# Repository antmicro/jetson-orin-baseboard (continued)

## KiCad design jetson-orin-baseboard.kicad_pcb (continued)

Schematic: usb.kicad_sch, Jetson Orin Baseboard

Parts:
C26, C27, C29, C31, C33, C36, C37, C38, C39, C45, C46, C47, C54, C55, C57, C60, C61, C62, C63: C_100n_0402; 0402-cap; MPN GRM155R61H104KE14D
C28, C30, C34, C35, C56, C59: C_10u_0402; 0402-cap; MPN CC0402MRX5R5BB106
C32: C_10u_25V_0603; 0603-cap; MPN C1608X5R1E106M080AC
C53, C58, C64, C65: C_100n_0402_50V; 0402-cap; MPN GRM155R71H104KE14D
D2, D3, D4, D5, D8, D9: LTST-C190GKT; LED_0603; MPN LTST-C190GKT
D6, D7: DF2S30FS; SOD-923; MPN DF2S30FS
D35: RB521S30T1G; SOD-523; MPN RB521S30T1G
J3: USB4105-GF-A; GCT_USB4105-GF-A; MPN USB4105-GF-A
J4: WE_632723300011_alt_symbol; WE_632723300011; MPN 632723300011
Q1, Q2, Q3: NX138BKMYL; DFN1006-3; MPN NX138BKMYL
R23, R24, R33: 4x0R_0201_array; EXB18V; MPN EXB-18VR000X
R40, R41, R56, R57, R58, R59, R60, R61, R65, R66, R67, R70, R71, R75, R76, R79, R80, R81, R82, R84: R_0R_0402; 0402-res; MPN ERJ2GE0R00X
R42, R44, R46, R47, R49, R74, R77, R83, R99: R_10k_0402; 0402-res; MPN CRCW040210K0FKEDHP
R43, R45, R105, R111: R_100k_0402; 0402-res; MPN CRCW0402100KFKEDHP
R68, R69, R72, R73, R106, R112: R_200R_0603; 0603-res; MPN ERJ-UP3F2000V
R78, R104: R_2k2_0402; 0402-res; MPN RC0402FR-072K2L
R85, R86, R87, R88, R89, R90, R91, R92, R93, R94, R95, R96, R97, R98: R_1k_0402; 0402-res; MPN CR0402-FX-1001GLF
R109, R110: R_2M0_0402; 0402-res; MPN AC0402FR-072ML
TP13, TP14, TP15, TP16, TP17, TP18, TP19, TP20, TP21, TP22, TP23, TP24, TP25, TP26, TP27, TP29: TP_SMD_0_75MM; Testpoint_smd_0_75mm
TP28: TP; TP-R-1.5
U5: FT230XQ-R; WQFN-16-1EP_4x4mm; MPN FT230XQ-R
U6: TPS65988; IC_TPS65987DDHRSHR; MPN TPS65988DHRSHR
U7: W25Q80DVUXIE_TR; USON-8_2x3mm_P0.5mm; MPN W25Q80DVUXIE TR
U8: TPS7B8133DRVR; WSON6_TI_2x2mm; MPN TPS7B8133DRVR
U9, U12: AP22615; TSOT23-6; MPN AP22615AWU-7
U10: TUSB1046-DCI; WQFN-40_1EP_6x3mm_Pitch0.4mm_EP4.7x2.7mm; MPN TUSB1046-DCIRNQT
U11, U13, U14, U15, U16: TPD4E05U06QDQARQ1; USON-10_2.5x1.0mm_P0.5mm; MPN TPD4E05U06QDQARQ1

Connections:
+1V8: Q1.1 (G), R47.2; also elsewhere on the board
+3V3: C26.1, C36.1, C37.1, C54.1, C55.1, C56.1, R49.2, R85.2, R87.2, R89.2, R91.2, R93.2, R95.2, R97.2, R106.2, R112.2, U6.5 (VIN_3V3), U10.1 (VCC), U10.6 (VCC), U10.20 (VCC), U10.28 (VCC); also elsewhere on the board
+5V: C35.1, C45.1, C57.1, C59.1, R74.2, R83.2, U6.25 (PP1_CABLE), U6.46 (PP2_CABLE), U9.6 (IN), U12.6 (IN); also elsewhere on the board
/USB Debug, DP/DRAIN1: U6.7 (DRAIN2), U6.52 (DRAIN2), U6.56 (DRAIN2), U6.57 (DRAIN2)
/USB Debug, DP/DRAIN2: U6.8 (DRAIN1), U6.15 (DRAIN1), U6.19 (DRAIN1), U6.58 (DRAIN1)
/USB Debug, DP/FLASH_CLK: R23.7, U7.6 (SCLK)
/USB Debug, DP/FLASH_MISO: R24.7, R24.8, U7.2 (SO/IO1)
/USB Debug, DP/FLASH_MOSI: R23.8, U7.5 (SI/IO0)
/USB Debug, DP/FTDI_3V3: C27.1, C29.1, C34.1, R46.2, R72.2, R73.2, U5.1 (VCCIO), U5.8 (3V3OUT), U5.10 (VCC), U8.6 (OUT)
/USB Debug, DP/FTDI_CBUS0: TP15.1, U5.12 (CBUS0)
/USB Debug, DP/FTDI_CBUS3: TP16.1, U5.14 (CBUS3)
/USB Debug, DP/FTDI_LED_RX: D3.2, U5.11 (CBUS1)
/USB Debug, DP/FTDI_LED_TX: D2.2, U5.5 (CBUS2)
/USB Debug, DP/HPDIN: R75.2, U10.32 (HPDIN/RSVD2)
/USB Debug, DP/LDO_3V3: D35.2
/USB Debug, DP/PDC_ADCIN1: R42.1, R43.2, U6.6 (ADCIN1)
/USB Debug, DP/PDC_ADCIN2: R44.1, R45.2, U6.10 (ADCIN2)
/USB Debug, DP/PDC_CTL0: R33.4, U6.18 (GPIO2)
/USB Debug, DP/PDC_CTL1: R33.2, U6.16 (GPIO0)
/USB Debug, DP/PDC_FLIP: R33.3, U6.17 (GPIO1)
/USB Debug, DP/PDC_GPIO14: R68.2, U6.42 (GPIO14/PWM1)
/USB Debug, DP/PDC_GPIO15: R69.2, U6.43 (GPIO15/PWM2)
/USB Debug, DP/PDC_HPD1: R65.2, U6.30 (GPIO3/HPD1)
/USB Debug, DP/PDC_I2C1_IRQn: TP17.1, U6.29 (~I2C1_IRQ)
/USB Debug, DP/PDC_I2C1_SCL: R70.2, U6.27 (I2C1_SCL)
/USB Debug, DP/PDC_I2C1_SDA: R71.2, U6.28 (I2C1_SDA)
/USB Debug, DP/PDC_I2C2_IRQn: TP18.1, U6.34 (~I2C2_IRQ)
/USB Debug, DP/PDC_I2C2_SCL: TP19.1, U6.32 (I2C2_SCL)
/USB Debug, DP/PDC_I2C2_SDA: TP20.1, U6.33 (I2C2_SDA)
/USB Debug, DP/PDC_I2C3_SCL: R66.2, U6.21 (I2C3_SCL/GPIO5)
/USB Debug, DP/PDC_I2C3_SDA: R67.2, U6.22 (I2C3_SDA/GPIO6)
/USB Debug, DP/PDC_LDO_1V8: C28.1, U6.35 (LDO_1V8)
/USB Debug, DP/PDC_LDO_3V3: C30.1, R42.2, R44.2, U6.9 (LDO_3V3)
/USB Debug, DP/PDC_RESET: R41.2, U6.44 (HRESET)
/USB Debug, DP/USBC0_5V_PEN: R84.1, U6.49 (GPIO17/PP_EXT2)
/USB Debug, DP/USBC0_CC1: J4.A5 (CC1), U6.45 (C2_CC1), U16.5 (IO4), U16.6 (IO4)
/USB Debug, DP/USBC0_CC2: J4.B5 (CC2), U6.47 (C2_CC2), U16.4 (IO3), U16.7 (IO3)
/USB Debug, DP/USBC0_CONN_TX1_N: C60.2, J4.A3 (TX1-), U15.5 (IO4), U15.6 (IO4)
/USB Debug, DP/USBC0_CONN_TX1_P: C62.2, J4.A2 (TX1+), U15.4 (IO3), U15.7 (IO3)
/USB Debug, DP/USBC0_CONN_TX2_N: C61.2, J4.B2 (TX2+), U14.4 (IO3), U14.7 (IO3)
/USB Debug, DP/USBC0_CONN_TX2_P: C63.2, J4.B3 (TX2-), U14.5 (IO4), U14.6 (IO4)
/USB Debug, DP/USBC0_CTL0: R33.6, R82.1, U10.22 (CTL0/SDA)
/USB Debug, DP/USBC0_CTL1: R33.5, U10.23 (CTL1/HPDIN)
/USB Debug, DP/USBC0_DPEQ0: R91.1, R92.1, U10.14 (DPEQ0/A1)
/USB Debug, DP/USBC0_DPEQ1: R93.1, R94.1, U10.2 (DPEQ1)
/USB Debug, DP/USBC0_EQ0: R95.1, R96.1, U10.38 (EQ0)
/USB Debug, DP/USBC0_EQ1: R97.1, R98.1, U10.35 (EQ1)
/USB Debug, DP/USBC0_FLG: R83.1, TP29.1, U12.3 (FLG)
/USB Debug, DP/USBC0_FLIP: R33.7, R79.1, U10.21 (FLIP/SCL)
/USB Debug, DP/USBC0_I2C_EN: R85.1, R86.1, U10.17 (I2C_EN)
/USB Debug, DP/USBC0_RX1_N: J4.B11 (RX1+), U10.31 (RX1_N), U15.2 (IO2), U15.9 (IO2)
/USB Debug, DP/USBC0_RX1_P: J4.B10 (RX1-), U10.30 (RX1_P), U15.1 (IO1), U15.10 (IO1)
/USB Debug, DP/USBC0_RX2_N: J4.A10 (RX2-), U10.39 (RX2_N), U14.1 (IO1), U14.10 (IO1)
/USB Debug, DP/USBC0_RX2_P: J4.A11 (RX2+), U10.40 (RX2_P), U14.2 (IO2), U14.9 (IO2)
/USB Debug, DP/USBC0_SBU1: J4.A8 (SBU1), R109.2, U10.27 (SBU1), U13.2 (IO2), U13.9 (IO2)
/USB Debug, DP/USBC0_SBU2: J4.B8 (SBU2), R110.2, U10.26 (SBU2), U13.1 (IO1), U13.10 (IO1)
/USB Debug, DP/USBC0_SSEQ0: R87.1, R88.1, U10.11 (SSEQ0/A0)
/USB Debug, DP/USBC0_SSEQ1: R89.1, R90.1, U10.3 (SSEQ1)
/USB Debug, DP/USBC0_TX1_N: C60.1, U10.34 (TX1_N)
/USB Debug, DP/USBC0_TX1_P: C62.1, U10.33 (TX1_P)
/USB Debug, DP/USBC0_TX2_N: C61.1, U10.36 (TX2_N)
/USB Debug, DP/USBC0_TX2_P: C63.1, U10.37 (TX2_P)
/USB Debug, DP/USBC0_VBUS: C65.1, D7.1, J4.A4 (VBUS), J4.A9 (VBUS), J4.B4 (VBUS), J4.B9 (VBUS), Q3.1 (G), R111.2, U6.3 (VBUS2), U12.1 (OUT)
/USB Debug, DP/USBC3_5V_PEN: R76.1, U6.48 (GPIO16/PP_EXT1)
/USB Debug, DP/USBC3_CC1: J3.A5 (CC1), U6.24 (C1_CC1), U11.5 (IO4), U11.6 (IO4)
/USB Debug, DP/USBC3_CC2: J3.B5 (CC2), U6.26 (C1_CC2), U11.4 (IO3), U11.7 (IO3)
/USB Debug, DP/USBC3_FLG: R74.1, TP27.1, U9.3 (FLG)
/USB Debug, DP/USBC3_VBUS: C32.1, C64.1, D6.1, J3.A4 (VBUS), J3.A9 (VBUS), J3.B4 (VBUS), J3.B9 (VBUS), Q2.1 (G), R105.2, U6.13 (VBUS1), U8.1 (IN), U8.2 (EN), U9.1 (OUT)
/USB Debug, DP/USBC_HPD1: Q1.3 (D), R49.1, R65.1, R75.1
/USB Debug, DP/USBPD_SCL: R61.1, R66.1, R70.1, R79.2
/USB Debug, DP/USBPD_SDA: R60.1, R67.1, R71.1, R82.2
/USB Debug, DP/USBSS0_RX_C_N: C38.2, U10.4 (SSRX_N)
/USB Debug, DP/USBSS0_RX_C_P: C46.2, U10.5 (SSRX_P)
/USB Debug, DP/USBSS0_TX_C_N: C39.2, U10.7 (SSTX_N)
/USB Debug, DP/USBSS0_TX_C_P: C47.2, U10.8 (SSTX_P)
/USB Debug, DP/USB_FTDI_N: R80.2, U5.7 (USBDM)
/USB Debug, DP/USB_FTDI_P: R81.2, U5.6 (USBDP)
/USB Debug, DP/~PFLASH_CS: R24.5, U7.1 (~CS)
/USB Debug, DP/~PFLASH_HOLD: R23.6, U7.7 (~HOLD/IO3)
/USB Debug, DP/~PFLASH_WP: R24.6, U7.3 (~WP/IO2)
DEBUG_RXD: R56.1; also elsewhere on the board
DEBUG_TXD: R57.1; also elsewhere on the board
DP1_AUX_N: U10.25 (AUX_N); also elsewhere on the board
DP1_AUX_P: U10.24 (AUX_P); also elsewhere on the board
DP1_HPD: R40.1; also elsewhere on the board
DP1_TXD0_N: U10.10 (DP0_N); also elsewhere on the board
DP1_TXD0_P: U10.9 (DP0_P); also elsewhere on the board
DP1_TXD1_N: U10.13 (DP1_N); also elsewhere on the board
DP1_TXD1_P: U10.12 (DP1_P); also elsewhere on the board
DP1_TXD2_N: U10.16 (DP2_N); also elsewhere on the board
DP1_TXD2_P: U10.15 (DP2_P); also elsewhere on the board
DP1_TXD3_N: U10.19 (DP3_N); also elsewhere on the board
DP1_TXD3_P: U10.18 (DP3_P); also elsewhere on the board
EEPROM_PWR: C33.1, D35.1, R23.3, R24.1, R24.3, TP21.1, U7.8 (VCC); also elsewhere on the board
GND: C26.2, C27.2, C28.2, C29.2, C30.2, C31.2, C32.2, C33.2, C34.2, C35.2, C36.2, C37.2, C45.2, C53.2, C54.2, C55.2, C56.2, C57.2, C58.2, C59.2, C64.2, C65.2, D4.2, D5.2, D6.2, D7.2, J3.A1 (GND), J3.A12 (GND), J3.B1 (GND), J3.B12 (GND), J3.S1 (SHIELD), J4.A1 (GND), J4.A12 (GND), J4.B1 (GND), J4.B12 (GND), J4.Shell (SHIELD), Q2.2 (S), Q3.2 (S), R41.1, R43.1, R45.1, R77.1, R78.1, R86.2, R88.2, R90.2, R92.2, R94.2, R96.2, R98.2, R99.1, R104.1, R105.1, R109.1, R110.1, R111.1, TP26.1, U5.3 (GND), U5.13 (GND), U5.17 (GND), U6.20 (GND), U6.51 (GND), U6.59 (GND_EP), U7.4 (VSS), U8.3 (GND), U8.4 (GND), U8.7 (GND), U9.2 (GND), U10.41 (EP_GND), U11.3 (GND), U11.8 (GND), U12.2 (GND), U13.3 (GND), U13.8 (GND), U14.3 (GND), U14.8 (GND), U15.3 (GND), U15.8 (GND), U16.3 (GND), U16.8 (GND); also elsewhere on the board
unnamed: C31.1, R46.1, U5.9 (~RESET)
unnamed: D2.1, R72.1
unnamed: D3.1, R73.1
unnamed: D4.1, R68.1
unnamed: D5.1, R69.1
unnamed: D8.1, R106.1
unnamed: D8.2, Q2.3 (D)
unnamed: D9.1, R112.1
unnamed: D9.2, Q3.3 (D)
unnamed: Q1.2 (S), R40.2, R47.1
unnamed: R56.2, U5.15 (TXD)
unnamed: R57.2, U5.2 (RXD)
unnamed: R58.2, U5.16 (~RTS)
unnamed: R59.2, U5.4 (~CTS)
unnamed: R76.2, R77.2, U9.4 (EN)
unnamed: R78.2, U9.5 (ISET)
unnamed: R84.2, R99.2, U12.4 (EN)
unnamed: R104.2, U12.5 (ISET)
unnamed: TP13.1, U6.31 (GPIO4/HPD2)
unnamed: TP14.1, U6.23 (~I2C3_IRQ/GPIO7)
unnamed: TP28.1, U10.29 (CAD_SNK/RSVD1)
PDC_MISO: R24.2, TP23.1, U6.36 (SPI_POCI/GPIO8); also elsewhere on the board
PDC_MOSI: R23.1, TP22.1, U6.37 (SPI_PICO/GPIO9); also elsewhere on the board
PDC_SCLK: R23.2, TP24.1, U6.38 (SPI_CLK/GPIO10); also elsewhere on the board
PWR_SOFT: R58.1; also elsewhere on the board
SYS_SCL: R61.2; also elsewhere on the board
SYS_SDA: R60.2; also elsewhere on the board
USB0_D_N: J4.A7 (D-), J4.B7 (D-), U16.2 (IO2), U16.9 (IO2); also elsewhere on the board
USB0_D_P: J4.A6 (D+), J4.B6 (D+), U16.1 (IO1), U16.10 (IO1); also elsewhere on the board
USBPD1_HV: C53.1, U6.11 (PP_HV1); also elsewhere on the board
USBPD2_HV: C58.1, U6.1 (PP_HV2); also elsewhere on the board
USBSS0_RX_N: C46.1; also elsewhere on the board
USBSS0_RX_P: C38.1; also elsewhere on the board
USBSS0_TX_N: C47.1; also elsewhere on the board
USBSS0_TX_P: C39.1; also elsewhere on the board
~PDC_CS: R24.4, TP25.1, U6.39 (~SPI_CS/GPIO11); also elsewhere on the board

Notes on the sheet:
USB-UART Bridge
POWER DOWN
USB PD Controller
USB-PD Source/Sink
USB-C 0 Display Port alt mode
4 LANE DP
CONFIGURATION
USBC0
Debug USB-C 3
USB + 2 LANE DP
USBC3
CTL0
CTL1
USB ONLY

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
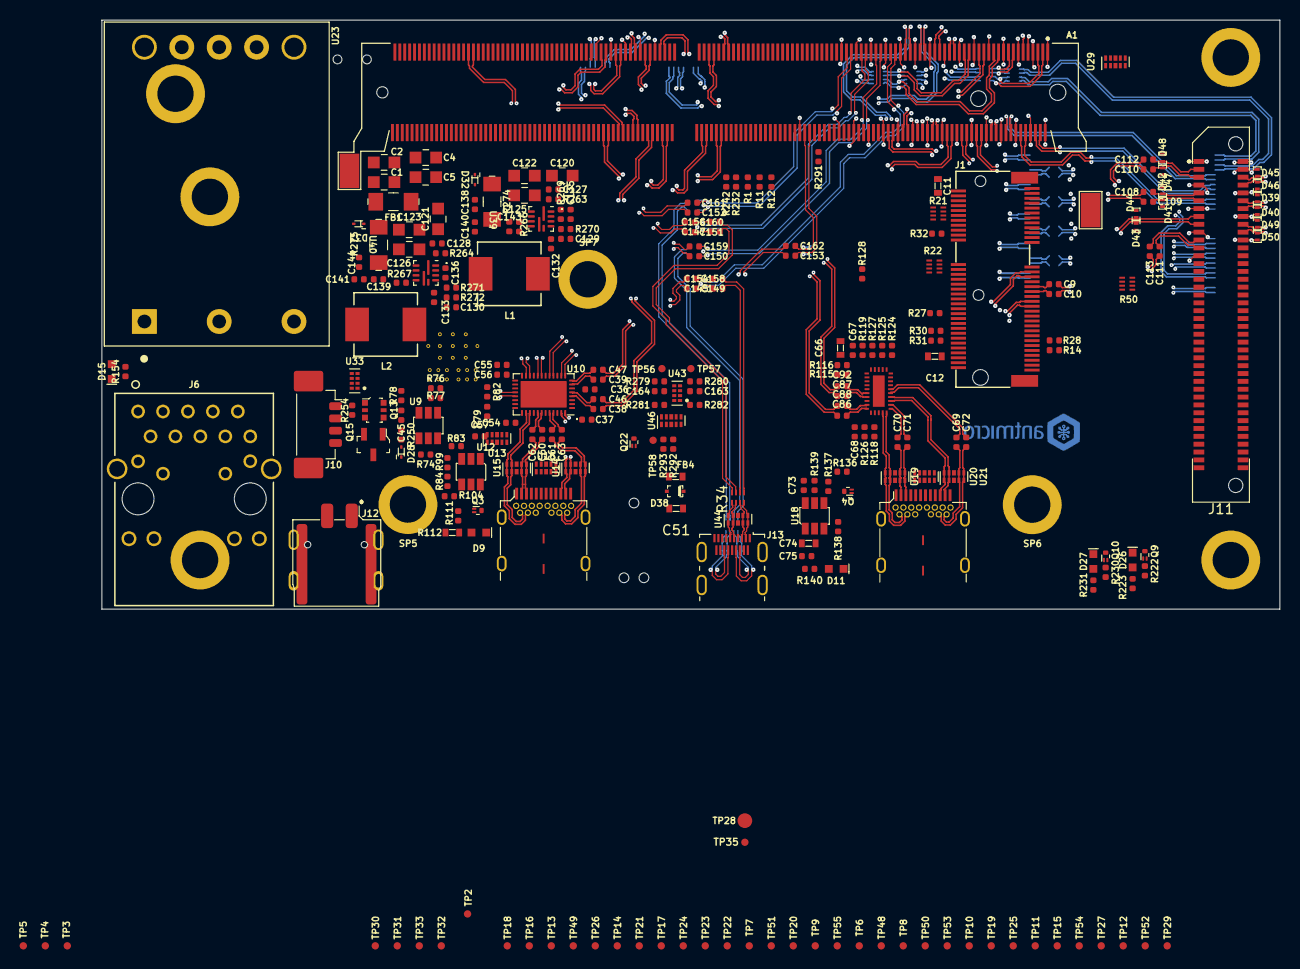
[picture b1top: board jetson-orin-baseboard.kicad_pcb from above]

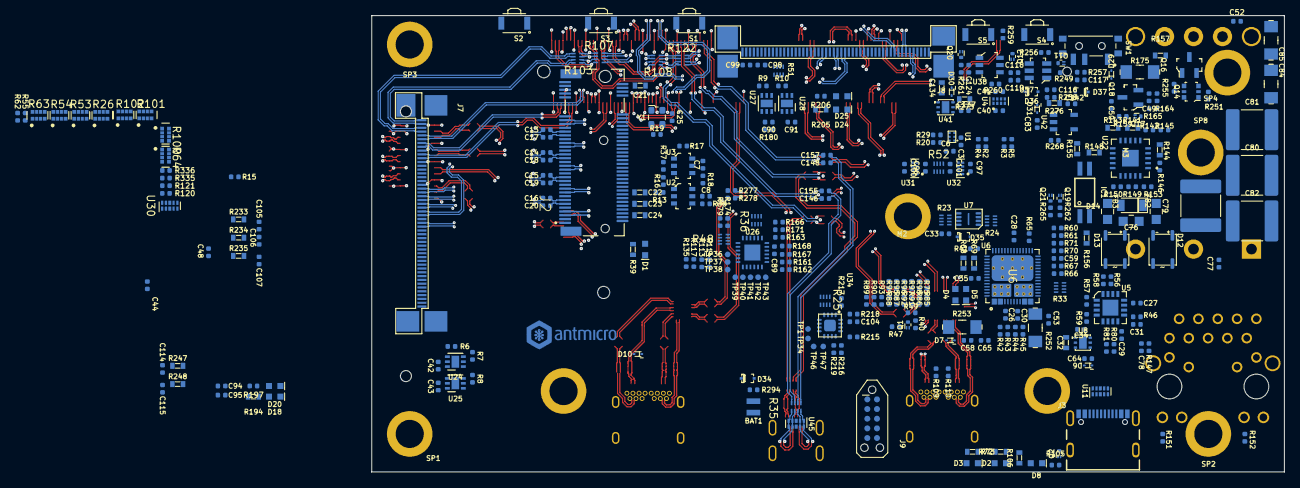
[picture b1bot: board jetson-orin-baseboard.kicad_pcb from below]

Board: 8 copper layers, 120.0 x 60.0 mm, 587 parts (331 on the bottom side), 599 nets.

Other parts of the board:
kibuzzard-633EE390: G***; kibuzzard-633EE390

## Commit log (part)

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2023-02-09 Enumerate resistors
2023-02-09 Replace buttons on PCB. Update VBUS led circuitry. Improve power planes
2023-02-09 Continue moving signals to accomodate new switch position
2023-02-10 Continue routing after changes
2023-02-13 Update PCB from schematics. Recover deleted footprints
2023-02-14 Clear space under new HDMI connector
2023-02-14 Change tag-connect to 2x5 pin 1.27 header
2023-02-14 Import changes from schematics. Finish signal routing
2023-02-14 Cleanup PCB with cleanup tool
2023-02-14 Minor layout improvements
2023-02-15 Start tunning high speed traces
2023-02-16 Add more capacitors to the SoM VDD_IN
2023-02-16 Place caps and resistors on PCB
2023-02-16 Fix custom design rules for differential pair
2023-02-16 Fix intra-pair sqew errors
2023-02-16 Route CSI_B_EN signal on bottom layer only
2023-02-17 Connect USB-C HPD to correct pin
2023-02-17 Place tag connect on the PCB. Update layout after recent schematic changes
2023-02-21 Import changes to PCB. Cleanup space for DP mux
2023-02-23 Routed DP++ signals to the display mux
2023-02-24 Added 499 Ohm resistors required for HDMI
2023-02-24 Added alternative DNP circuitry to make DP priority
2023-02-28 Fix SDA/SCL cross
2023-02-28 Replace 1u/10V cap with 1u/25V one
2023-02-28 Add capacitors to USB SS. Add VBUS, _HV 1u/4u7 caps. Improve readability
2023-02-28 Update J8 VSYNC singal assigment
2023-03-01 Add ESD protection to force recovery button
2023-03-01 Add 10k pullups to I2C1/I2C2 signals
2023-03-01 Add 220k pullups to HD3SS3220 OUTx pins
2023-03-01 Add TVS to the J14
2023-03-01 Minor readability improvements
2023-03-01 Update PCM12SMTR symbol
2023-03-01 Add resistor to slow down discharge of U37 2A input. Add TVS to S4 and S5
2023-03-01 Clarify auto startup comments
2023-03-01 Annotate parts, import them on PCB
2023-03-01 Start placement of the new components
2023-03-02 Simplify U6 I2C connection. Adjust pinout on R80/R81 remove flash R0 arrays
2023-03-02 Flip connections on R26 and R63 for easier routing
2023-03-02 Adjust connections on R130 for easier routing
2023-03-02 Improve clearance around PoE signals
2023-03-02 Minor improvements around U10
2023-03-02 Simplify routing around J11
2023-03-02 Improve U34 fanout
2023-03-02 Add thermal relief for M.2 key E and CSI A
2023-03-03 Fix silks warnings
2023-03-03 Add labels to M.2 connectors and ETH
2023-03-03 Bump revision to 1.1.0
2023-03-03 Add USB_ID controll from USB-C1 VBUS. Clarify notes
2023-03-03 Implement changes on PCB
2023-03-03 Fix M.2 Key M label
2023-03-06 Set R199 and R229 as DNP. U23 has builtin pullup on CTRL pin
2023-03-06 Connect power switches FLG pins to the GPIO expander
2023-03-06 Use AP22615 as CSI e-fuse
2023-03-06 Enumerate components. Import to PCB. Update layout with new components
2023-03-06 Minor via improvements around 5V and 3.3V DCDC
2023-03-08 Add diagram to readme
2023-03-08 Use PNG diagram in readme
2023-03-08 Set USB_PD_IRQ label as output on usb subsheet
2023-03-08 Update CSIA/B_FLG label naming
2023-03-08 Update HD3SS3220 and TPS65988 IRQ pins circuitry to use 1.8V singaling
2023-03-08 Update layout after schematic changes. Place components, clear DRC and silks
2023-04-11 README: rephrase, mention Jetson Orin Nano
2023-07-05 Ethernet Simplification
2023-10-16 Introduce component standardization
2023-10-20 Fixed HDMI 3d model offset
2023-11-06 Updated few symbols/footprints with newest version from the library
2023-11-06 Add OHP assets
2023-11-06 Add stackup.csv
2024-01-05 [#53466] pcb: swap CSIA_5V and CSIA_3V3 LEDs labels
2024-01-05 [#53466] pcb: use ${REVISION} in the revision string on PCB
2024-03-22 [#56923] Update symbol/footprint links; Migrate to KiCad 7
2024-03-26 [#56923] Fix OHP issue
2024-03-26 [#56923] Loclib
2024-03-27 Update assets
2024-03-29 [#56923] Cleaned up DRC, restored old H2.5mm footprint
2024-03-29 [#56923] Restored DRC and minor designator cleanup
2024-05-27 [#59786] Update SoM standoffs
2024-05-27 [#59786] Exclude J9 from BoM
2024-05-28 [#60110] Add BAT1 polarity marking
2024-05-29 [#60168] Update TagConnect symbol and footprint
2024-05-29 [#60168] Update R_499R_0402 and R_887k_0402 from library
2024-05-29 [#60168] Update Y1, BA1, C_47p_0402 symbols and footprints
2024-05-29 [#60168] Update SoM connector symbol and footprint
2024-05-29 [#60168] Update C_47p_0402 symbols and footprints
2024-06-03 [#60168] Update C_220n_0402 symbols and footprints
2024-06-03 [#60168] Update LED_G_0603_LTST-C190GKT symbols
2024-06-04 [#60168] Update Tag-Connect_TC2050 symbols and footprints
2024-06-04 [#60168] Change the DDR4 socket footprint from Bus_DDR4_SODIMM_TE_2309413 to TE_2309413
2024-06-04 [#60168] Update coper logos to global lib
2024-06-05 [#60168] Revert D54 position
2024-06-05 [#60168] Fix silkscreen warnings
2024-06-05 [#60168] Relink 3D modles to global lib, assign missing 3D models
2024-06-05 [#60168] Improve passive components silkscreen
2024-06-05 [#60168] Add comment about DC in connector
2024-06-13 [#60110] Add PoE netclass. Increase PoE clereance
2024-06-14 [#60110] Fixed HS routing. Fixed silkscreen
2024-06-14 [#60110] Updated pdf schematics
2024-06-14 [#60110] Updated VCC_CONN voltage description
2024-07-01 README: Update OHP links, bump copyright date
2024-07-01 [#61641] Update TPS65988DHRSHR footprint
2024-07-01 [#61641] Updated pcb fill
2024-07-26 Add documentation for GitHub Pages
2024-07-26 Fix J3 on IO map
2024-07-29 Add 3D renders presenting board connections
2024-07-30 Rename docs folder
2024-07-30 README: Update doc folder name
2024-07-30 Updated renders and altered description of power supply connection
2024-07-30 update 8e9fef7b4b0b629bf49db563b7ea2beb83c7b6ea
2024-08-16 [#61587] Layout update after DRC adjustment
2024-08-16 [#61587] Fix length matching. Bump revision to 1.1.7
2024-08-16 [#61587] Synchronize component instances
2024-08-16 [#61587] Cleanup design after component synchronization
2024-08-16 [#61587] Correct R42 value back to 10k
2024-08-16 [#61587] Add power flags on schematic
2024-08-16 [#61587] Add polarity marking on Molex Nano-Fit connector
2024-08-19 [#63764] Minor language fixes
2024-08-23 64668 Describe USB-C as a recommended power supply option
2024-08-29 [#64774] upload assets
2024-08-29 Include recent updates to docs
2024-08-29 Add referenced images and links to docs
2024-09-02 [#64687] Fix references
2024-09-03 [#64267] Remove local symbol and footprint paths
2024-09-03 [#64267] Remove old DC-DC converters from PCB, start layout of new ones
2024-09-03 [#64267] Change resistors to set the PD controller to configuration 3
2024-09-03 [#64267] Swap 5V and 3V3 converter placement
2024-09-03 [#64267] Layout components for +5V power path
2024-09-03 [#64267] Try new component placement of 3V3 converter, new coil
2024-09-03 [#64267] Replace the coil for the 5V converter
2024-09-03 [#64267] Finish layout of 3V3 converter
2024-09-03 [#64602] Fix some tracks and silkscreen
2024-09-03 [#64602] Add resistor divider for UVLO for 5V converter, repair last broken tracks, adjust silkscreen
2024-10-07 [#64602] Update component footprints from library, increase clearance between GND and 3V3 switching node, clear DRC
2024-10-07 [#64336] Update SPI net names
2024-10-07 [#64336] Add tag connect pinout on silkscreen
2024-10-07 [#64336] Update SPI connector pinout, finish layout
2024-10-07 [#64336] Align component designators and restore missing logos
2024-10-07 [#64336] Swap SPI and I2C information on silkscreen
2024-10-07 [#64336] Move R112 to the bottom
2024-10-07 [#64336] Clear DRC
2024-10-07 [#64336] Improve R131 connection
2024-10-07 [#64790] Move C130, adjust designators, upgrade tespoints markings
2024-10-07 [#64790] Adjust designators and polygons, improve tespoints
2024-10-07 [#64790] Clean DRC
2024-10-07 [#64336] Align text fields inside the SPI pinout
2024-10-07 [#64928] Implemented fixes after layout review
2024-10-07 [#64928] Implement fixes after schematic review
2024-10-07 [#64928] Correct names of fiducials on PCB, add not in schematic property to all of them
2024-10-07 Updated assets for rev. 1.1.8
2024-10-07 [#64928] Relocate test points to accessible areas
2024-10-07 [#64928] Add more test points, small tweaks on silkscreen layers
2024-10-07 Updated docs to reflect changes in rev. 1.1.8
2024-10-07 [#64928] Update footprints from library, clean DRC and ERC
2024-10-07 [#64928] Place components, start routing signals
2024-10-07 [#64928] Add DNP 10M pulldown to Q20, fix note, Replace U29 with NTS0102GT
2024-10-07 [#66619] Update layout
2024-10-07 [#64928] Align designators
2024-10-07 [#66619] Refresh assets
2024-10-14 [#67155] Fix annular ring on Inner copper 1 layer
2024-10-14 [#67155] Bump project date
2024-10-14 [#67155] Bump rev to 1.2.0
2024-10-14 [#67155] Exclude 5V DCDC coil overlap DRC
2024-10-14 [#67155] Add pin driven errors to exclusions
2024-10-14 [#67155] Update unactual component symbols
2024-10-14 [#67155] Update ERC
2024-10-14 [#67155] Update PCB from schematic
2024-10-15 [#67155] Update expansion connector VCC comment
2024-10-15 [#67339] Add custom rule for hole to track clearance
2024-10-15 [#67339] Resize vias to 0.2hole, update filled zones
2024-10-16 [#67339] Remove custom rule
2024-10-16 [#67339] Resize vias to 0.1mm hole, bump revision
2024-10-17 [#67339] Update USB3 mode selector frame
2024-10-17 [#67339] Update connections on In1.Cu
2024-10-18 [#67339] Fix USBC1_CONN_TX2 traces
2024-11-06 update bc5568f82e9669cea81eb16c524d8fbed8b4e56d
2024-11-20 [#68531] Migrate to kicad8
2024-11-20 [#68531] Update kicad version in docs/readme
2024-11-22 [#69189] Fix swapped designators, bump revision to 1.2.2
2024-11-22 [#69189] Fix ERC
2024-11-26 [#69189] Clean DRC
2024-11-26 [#69189] Add schematic ERCs
2024-11-26 [#69189] Add layout DRC exclusions
2024-11-29 [#69516] Perform kmake dnp
2024-11-29 [#69516] Update 22u 0603 capacitor symbol
2024-11-29 [#69516] Update 22u 0603 capacitor footprints
2024-11-29 [#69516] Bump revision to 1.2.3
2024-11-29 [#69516] Update assets
2025-01-15 [#71466] Add support for Orin NX Super VDD requirement: layout
2025-01-15 [#71466] Clear ERC and DRC, improve power traces, mark slew rate control capacitors in ideal diodes as DNP
2025-01-15 [#71466] Bump revision to 1.3.0
2025-01-21 [#71466] Fix date on the PCB and GbE spacing
2025-01-21 [#71466] WIP: Fix ideal diodes
2025-01-21 [#71466] Fit R272 and move traces and components around
2025-01-21 [#71466] Unrouted 0
2025-01-21 [#71466] Slightly move R274 and R275 in order to clean DRC
2025-01-21 [#71466] Clear all DRC problems
2025-01-23 [#71466] Improve routing
2025-01-24 [#71764] Update documentation
2025-01-27 [#71764] Improve power labels on schematic
2025-01-27 [#71764] Improve power planes on PCB
2025-01-31 [#71764] Improve VDD_SoM power plane connection
2025-02-04 Reduce docs requirements
2025-02-04 Update date in (C)
2025-02-06 [#70607] Docs DC-DC stress tests
2025-02-11 Added kiri to gitignore
2025-02-11 [#72863] Marked dvdt caps as not DNP
2025-02-11 [#72863] Increased width of VCC plane
2025-02-12 [#72863] Removed problematic via in pads
2025-02-13 [#72863] Improve FTDI_CBUS_EN routing
2025-02-17 [#73151] Replace buttons at schematic
2025-02-17 [#73151] ReplBump revision
2025-02-17 [#73151] Connect buttons
2025-02-17 [#73151] Reposition LEDs
2025-02-17 [#73151] Resolve DRC
2025-02-17 [#73151] Increase clearance around buttons
2025-02-17 [#73151] Complete DRC
2025-02-18 [#73151] Update assets
2025-02-27 Import docs build as separate yml
2025-02-27 Fixed colors on gmsl topology graph
2025-03-07 [#74297] Add top and bottom photos of JOB rev.1.3.2
2025-03-10 update 8ba623ac2cec67e02384fe06a4e5436bc7070d6e
2025-03-14 [#74465] Correct revision and date on schematic sheets
2025-03-19 [#74460] Replace FB1 with 0R for SoM_VIN stability under high load
2025-03-20 [#74772] doc: drop the GMSL chapter
    GMSL documentation has been moved to demo description in meta-antmicro.
2025-03-25 update 7dbf7e1c6f9847132844f134d1beac2bbb8c0125
2025-05-05 [#74775] Added jetpack 6.x links
2025-05-05 README: Expand the list of compatible accessories
2025-05-21 [#77466] Update BSP links
2025-05-21 update 0f653f8a0557ee755067fe13fd946a8295dfdd79
2025-06-20 Bump CI template
2025-07-15 [#80029] Update BSP links
2025-07-15 update 824445d8e621b3581df0f77e61a858a82e45fc40
2026-02-13 Add 2026 to copyright
2026-02-23 Add link to the Orin series
2026-02-23 README: add USB as expansion interface
2026-04-07 Fix SD link
2026-05-15 Doc: Add note about HDMI cables
